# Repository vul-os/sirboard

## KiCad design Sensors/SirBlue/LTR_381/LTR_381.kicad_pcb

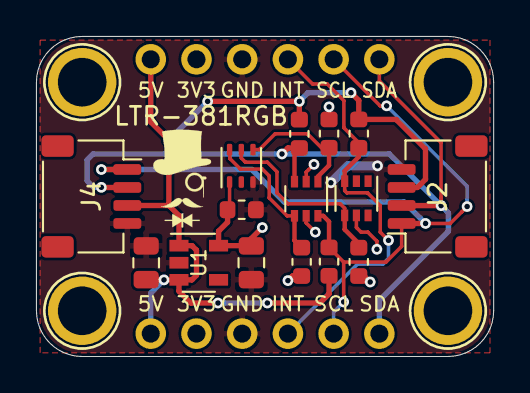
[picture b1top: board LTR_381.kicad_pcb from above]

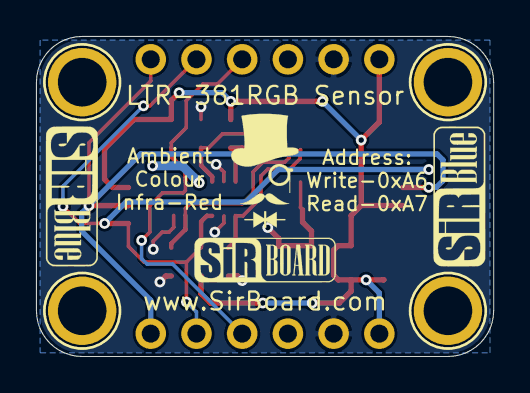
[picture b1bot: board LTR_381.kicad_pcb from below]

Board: 2 copper layers, 25.4 x 17.8 mm, 21 parts (2 on the bottom side), 9 nets.

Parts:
C1, C4: 10uF; C_0805_2012Metric
C2: 100nF; C_0603_1608Metric
H1, H2, H3, H4: MountingHole; MountingHole_M2.5_SirBoard
J1, J3: Conn_01x06; PinHeader_1x06_P2.54mm_Vertical
J2, J4: Conn_01x04; JST_SH_SM04B-SRSS-TB_1x04-1MP_P1.00mm_Horizontal
LTR-381RGB: LTR-381RGB-WA; Lite-On_LTR-303ALS-01
Q1, Q2: BSS138DW; SOT-363_SC-70-6
R3, R4, R5, R6, R7, R8: 10K; R_0603_1608Metric
U1: AP2127K-3.3; SOT-23-5

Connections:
3V3: C2.1, C4.1, J1.2, J3.2, LTR-381RGB.1, Q1.5, Q2.2, Q2.5, R3.2, R5.2, R7.2, U1.5
5V: C1.1, J1.1, J2.3, J3.1, J4.3, R4.1, R6.1, R8.1, U1.1, U1.3
GND: C1.2, C2.2, C4.2, J1.3, J2.4, J3.3, J4.4, LTR-381RGB.3, U1.2
INT_3V3: LTR-381RGB.5, Q1.4, R3.1
INT_5V: J1.4, J3.4, Q1.3, R4.2
SCL_3V3: LTR-381RGB.4, Q2.1, R5.1
SCL_5V: J1.5, J2.1, J3.5, J4.1, Q2.6, R6.2
SDA_3V3: LTR-381RGB.6, Q2.4, R7.1
SDA_5V: J1.6, J2.2, J3.6, J4.2, Q2.3, R8.2

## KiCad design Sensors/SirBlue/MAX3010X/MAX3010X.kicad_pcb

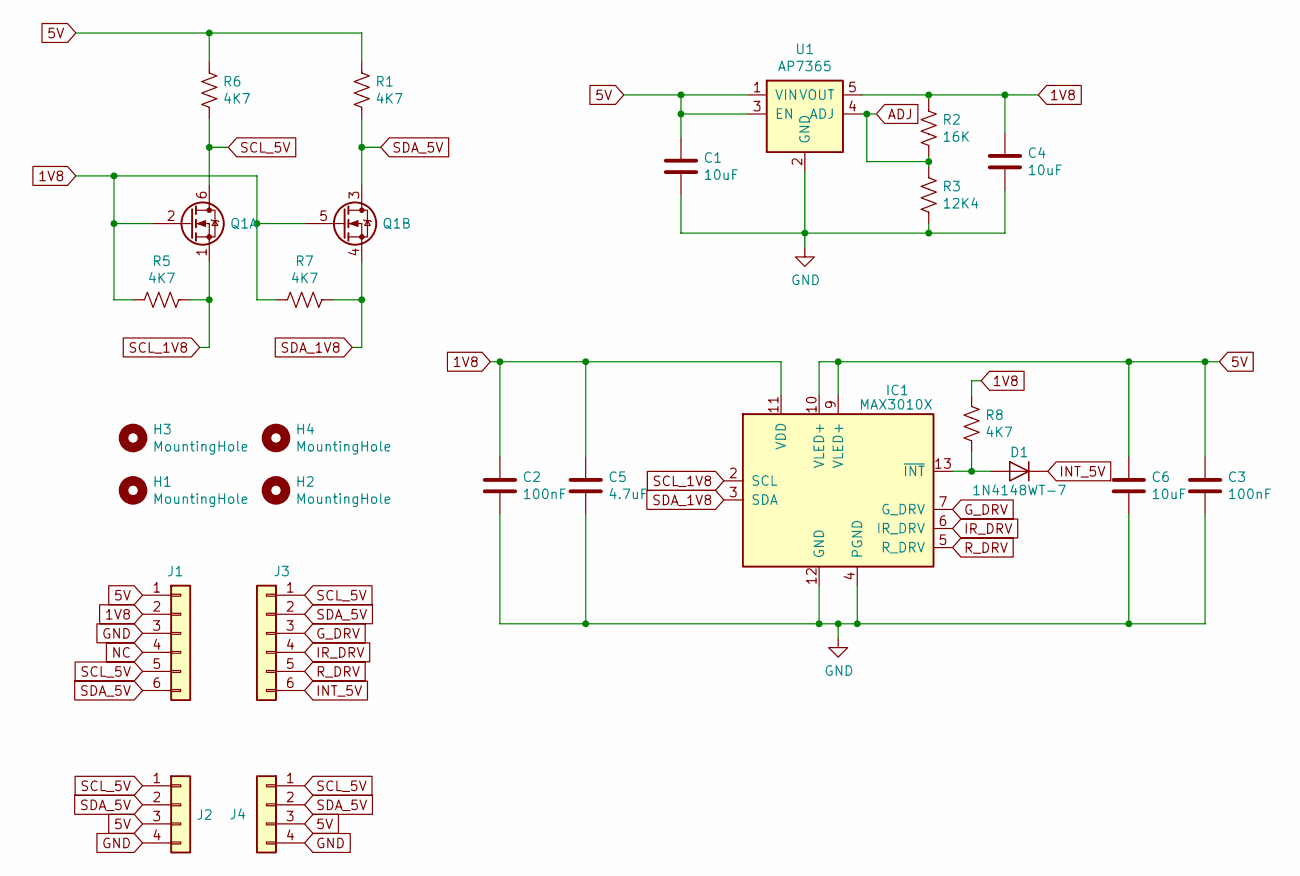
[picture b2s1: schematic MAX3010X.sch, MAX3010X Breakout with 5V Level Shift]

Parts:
C1, C4, C6: 10uF; C_0805_2012Metric; Part C95841
C2, C3: 100nF; C_0603_1608Metric; Part C42998
C5: 4.7uF; C_0805_2012Metric; Part C87998
D1: 1N4148WT-7; D_SOD-523; Part C83482
H1, H2, H3, H4: MountingHole; MountingHole_M2.5_SirBoard
IC1: MAX3010X; Maxim_OLGA-14_3.3x5.6mm_P0.8mm
J1, J3: Conn_01x06; PinHeader_1x06_P2.54mm_Vertical
J2, J4: Conn_01x04; SirBlue_Connector; Part C160404
Q1: BSS138DW; SOT-363_SC-70-6
R1, R5, R6, R7, R8: 4K7; R_0603_1608Metric; Part C99782
R2: 16K; R_0603_1608Metric; Part C4210
R3: 12K4; R_0603_1608Metric; Part C139128
U1: AP7365; SOT-23-5; Part C264087

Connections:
1V8: C2.1, C4.1, C5.1, IC1.11 (VDD), J1.2, Q1.2 (G), Q1.5 (G), R2.1, R5.2, R7.2, R8.1, U1.5 (VOUT)
5V: C1.1, C3.1, C6.1, IC1.9 (VLED+), IC1.10 (VLED+), J1.1, J2.3, J4.3, R1.1, R6.1, U1.1 (VIN), U1.3 (EN)
ADJ: R2.2, R3.1, U1.4 (ADJ)
GND: C1.2, C2.2, C3.2, C4.2, C5.2, C6.2, IC1.4 (PGND), IC1.12 (GND), J1.3, J2.4, J4.4, R3.2, U1.2 (GND)
G_DRV: IC1.7 (G_DRV), J3.3
INT_5V: D1.1 (K), J3.6
IR_DRV: IC1.6 (IR_DRV), J3.4
NC: J1.4
unnamed: D1.2 (A), IC1.13 (~INT), R8.2
R_DRV: IC1.5 (R_DRV), J3.5
SCL_1V8: IC1.2 (SCL), Q1.1 (S), R5.1
SCL_5V: J1.5, J2.1, J3.1, J4.1, Q1.6 (D), R6.2
SDA_1V8: IC1.3 (SDA), Q1.4 (S), R7.1
SDA_5V: J1.6, J2.2, J3.2, J4.2, Q1.3 (D), R1.2

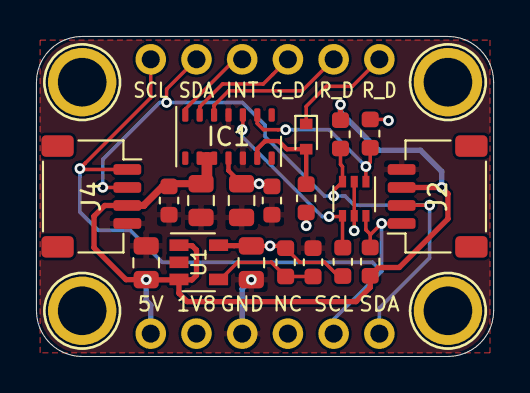
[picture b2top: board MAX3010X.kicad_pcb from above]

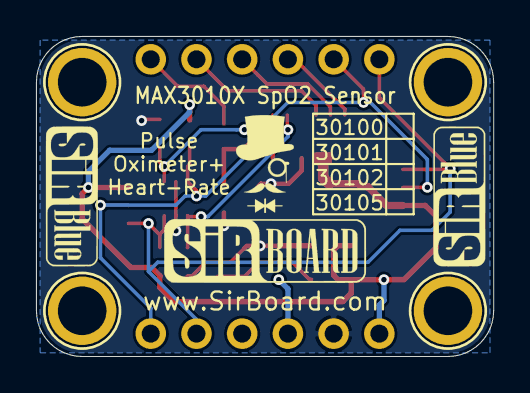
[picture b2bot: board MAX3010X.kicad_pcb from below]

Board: 2 copper layers, 25.4 x 17.8 mm, 25 parts (2 on the bottom side), 13 nets.

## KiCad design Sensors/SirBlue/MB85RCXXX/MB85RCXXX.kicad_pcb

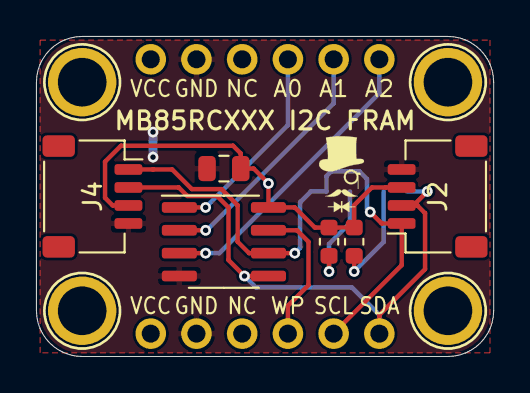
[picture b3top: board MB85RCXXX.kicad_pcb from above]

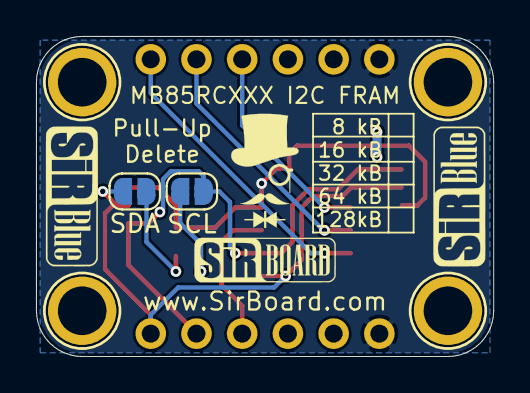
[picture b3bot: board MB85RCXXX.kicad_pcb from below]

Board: 2 copper layers, 25.4 x 17.8 mm, 14 parts (4 on the bottom side), 10 nets.

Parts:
C1: 10uF; C_0805_2012Metric
H1, H2, H3, H4: MountingHole; MountingHole_M2.5_SirBoard
J1, J3: Conn_01x06; PinHeader_1x06_P2.54mm_Vertical
J2, J4: Conn_01x04; JST_SH_SM04B-SRSS-TB_1x04-1MP_P1.00mm_Horizontal
R1, R2: 10K; R_0603_1608Metric
SCL: SolderJumper_2_Open; SolderJumper-2_P1.3mm_Open_RoundedPad1.0x1.5mm
SDA: SolderJumper_2_Open; SolderJumper-2_P1.3mm_Open_RoundedPad1.0x1.5mm
U1: MB85RCXXX; SOIC-8_3.9x4.9mm_P1.27mm

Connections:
A0: J3.4, U1.1
A1: J3.5, U1.2
A2: J3.6, U1.3
GND: C1.2, J1.2, J2.4, J3.2, J4.4, U1.4
unnamed: R1.2, SCL.2
unnamed: R2.2, SDA.2
SCL: J1.5, J2.1, J4.1, SCL.1, U1.6
SDA: J1.6, J2.2, J4.2, SDA.1, U1.5
VCC: C1.1, J1.1, J2.3, J3.1, J4.3, R1.1, R2.1, U1.8
WP: J1.4, U1.7

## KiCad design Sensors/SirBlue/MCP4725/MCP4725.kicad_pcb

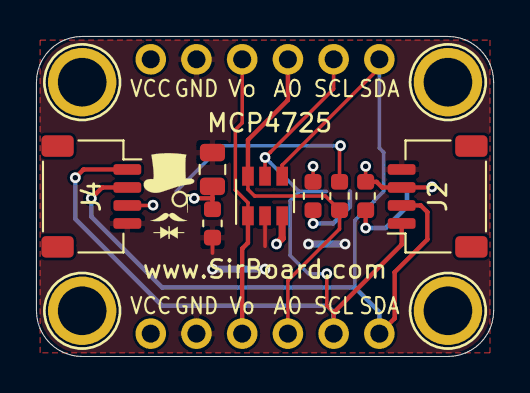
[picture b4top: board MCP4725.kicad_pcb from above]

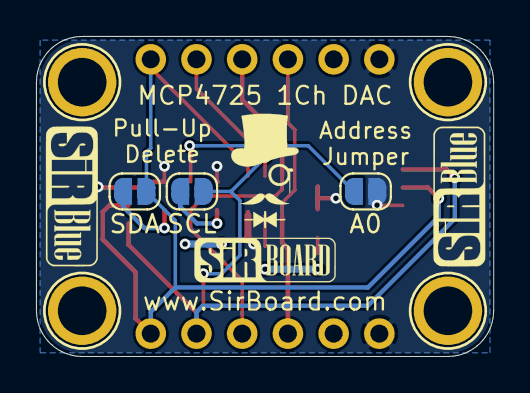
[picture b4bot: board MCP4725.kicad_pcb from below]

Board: 2 copper layers, 25.4 x 17.8 mm, 17 parts (5 on the bottom side), 9 nets.

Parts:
A0: SolderJumper_2_Open; SolderJumper-2_P1.3mm_Open_RoundedPad1.0x1.5mm
C1: 10uF; C_0805_2012Metric
C5: 100nF; C_0603_1608Metric
H1, H2, H3, H4: MountingHole; MountingHole_M2.5_SirBoard
J1, J3: Conn_01x06; PinHeader_1x06_P2.54mm_Vertical
J2, J4: Conn_01x04; JST_SH_SM04B-SRSS-TB_1x04-1MP_P1.00mm_Horizontal
R1, R2, R3: 10K; R_0603_1608Metric
SCL: SolderJumper_2_Open; SolderJumper-2_P1.3mm_Open_RoundedPad1.0x1.5mm
SDA: SolderJumper_2_Open; SolderJumper-2_P1.3mm_Open_RoundedPad1.0x1.5mm
U1: MCP4725; SOT-23-6

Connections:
A0: J1.4, J3.4, R3.2, U1.6
GND: C1.2, C5.2, J1.2, J2.4, J3.2, J4.4, U1.2
unnamed: A0.2, R3.1
unnamed: R1.2, SCL.2
unnamed: R2.2, SDA.2
SCL: J1.5, J2.1, J3.5, J4.1, SCL.1, U1.5
SDA: J1.6, J2.2, J3.6, J4.2, SDA.1, U1.4
VCC: A0.1, C1.1, C5.1, J1.1, J2.3, J3.1, J4.3, R1.1, R2.1, U1.3
Vout: J1.3, J3.3, U1.1

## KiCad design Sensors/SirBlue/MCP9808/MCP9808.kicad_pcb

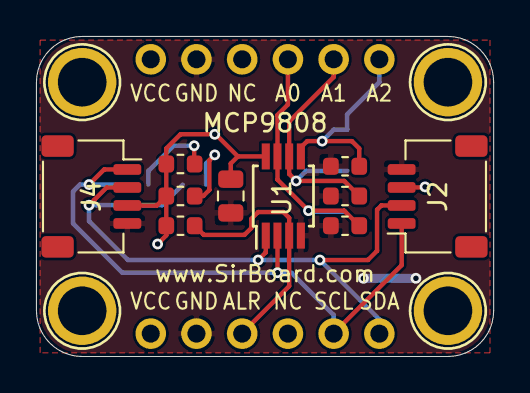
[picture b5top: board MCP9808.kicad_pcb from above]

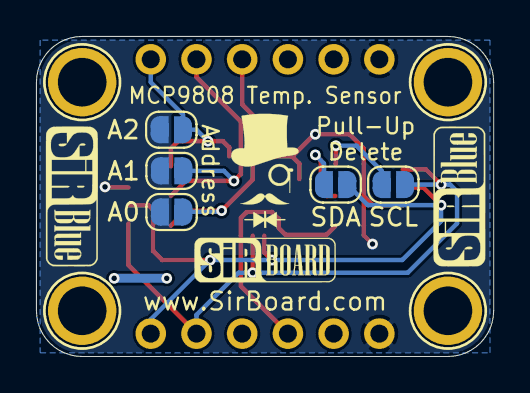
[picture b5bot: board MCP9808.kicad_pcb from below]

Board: 2 copper layers, 25.4 x 17.8 mm, 21 parts (7 on the bottom side), 10 nets.

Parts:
A0, A1, A2: SolderJumper_2_Open; SolderJumper-2_P1.3mm_Open_RoundedPad1.0x1.5mm
C1: 10uF; C_0805_2012Metric
H1, H2, H3, H4: MountingHole; MountingHole_M2.5_SirBoard
J1, J3: Conn_01x06; PinHeader_1x06_P2.54mm_Vertical
J2, J4: Conn_01x04; JST_SH_SM04B-SRSS-TB_1x04-1MP_P1.00mm_Horizontal
R1, R2, R3, R4, R5, R6: 10K; R_0603_1608Metric
SCL: SolderJumper_2_Open; SolderJumper-2_P1.3mm_Open_RoundedPad1.0x1.5mm
SDA: SolderJumper_2_Open; SolderJumper-2_P1.3mm_Open_RoundedPad1.0x1.5mm
U1: MCP9808_MSOP; MSOP-8_3x3mm_P0.65mm

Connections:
A0: A0.1, J3.4, R5.1, U1.7
A1: A1.1, J3.5, R4.1, U1.6
A2: A2.1, J3.6, R3.1, U1.5
ALERT: J1.3, R6.2, U1.3
GND: C1.2, J1.2, J2.4, J3.2, J4.4, R3.2, R4.2, R5.2, U1.4
unnamed: R1.2, SDA.2
unnamed: R2.2, SCL.2
SCL: J1.5, J2.1, J4.1, SCL.1, U1.2
SDA: J1.6, J2.2, J4.2, SDA.1, U1.1
VCC: A0.2, A1.2, A2.2, C1.1, J1.1, J2.3, J3.1, J4.3, R1.1, R2.1, R6.1, U1.8

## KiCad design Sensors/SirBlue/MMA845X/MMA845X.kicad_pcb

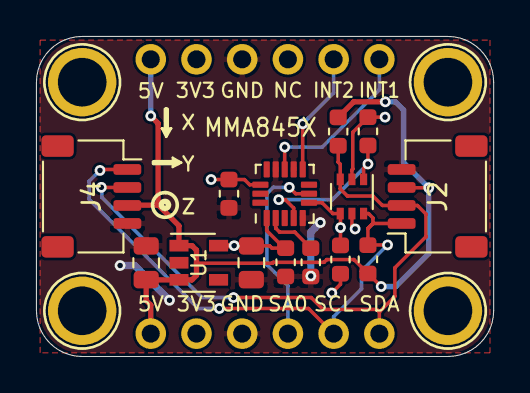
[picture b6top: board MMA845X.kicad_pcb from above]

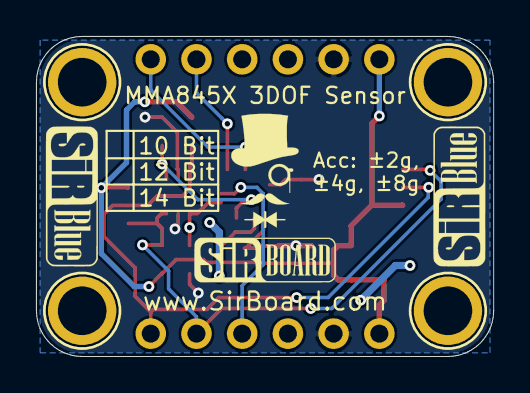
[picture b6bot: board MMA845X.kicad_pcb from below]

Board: 2 copper layers, 25.4 x 17.8 mm, 20 parts (2 on the bottom side), 11 nets.

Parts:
C1, C4: 10uF; C_0805_2012Metric
C2, C3, C5: 100nF; C_0603_1608Metric
H1, H2, H3, H4: MountingHole; MountingHole_M2.5_SirBoard
J1, J3: Conn_01x06; PinHeader_1x06_P2.54mm_Vertical
J2, J4: Conn_01x04; JST_SH_SM04B-SRSS-TB_1x04-1MP_P1.00mm_Horizontal
Q2: BSS138DW; SOT-363_SC-70-6
R5, R6, R7, R8: 10K; R_0603_1608Metric
U1: AP2127K-3.3; SOT-23-5
U2: MMA8451; QFN-COL-16-P=0.5

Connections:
3V3: C2.1, C4.1, C5.1, J1.2, J3.2, Q2.2, Q2.5, R5.2, R7.2, U1.5, U2.1, U2.14
5V: C1.1, J1.1, J2.3, J3.1, J4.3, R6.1, R8.1, U1.1, U1.3
GND: C1.2, C2.2, C3.2, C4.2, C5.2, J1.3, J2.4, J3.3, J4.4, U1.2, U2.5, U2.10, U2.12
INT1: J3.6, U2.11
INT2: J3.5, U2.9
unnamed: C3.1, U2.2
SA0: J1.4, U2.7
SCL_3V3: Q2.1, R5.1, U2.4
SCL_5V: J1.5, J2.1, J4.1, Q2.6, R6.2
SDA_3V3: Q2.4, R7.1, U2.6
SDA_5V: J1.6, J2.2, J4.2, Q2.3, R8.2
